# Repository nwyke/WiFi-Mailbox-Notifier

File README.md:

# WiFi Mailbox Notifier

This board notifies you when you get mail. JST-PH connector for 3.7V lithium ion battery (min 500mA), USB connector for power and battery charging, auto-reset for ESP-module, battery voltage measurement. 

Inspired by [hal9k "postkasse overvaagning"](https://hal9k.dk/postkasse-overvaagning/). Boards can be found on [OSHPark](https://oshpark.com/shared_projects/7UJ1nXM0) (not tested yet!).

Please support us and open-source hardware by purchasing products from
[MiniElektro.dk](http://minielektro.dk)/[MiniElektro.se](http://minielektro.se).

Content
-------------------
* **/Hardware**
  * All Eagle design files (.brd, .sch)
  * PDF schematic
  * BOM

License
-------------------
The hardware is released under [Creative Commons ShareAlike 4.0 International](https://creativecommons.org/licenses/by-sa/4.0/).

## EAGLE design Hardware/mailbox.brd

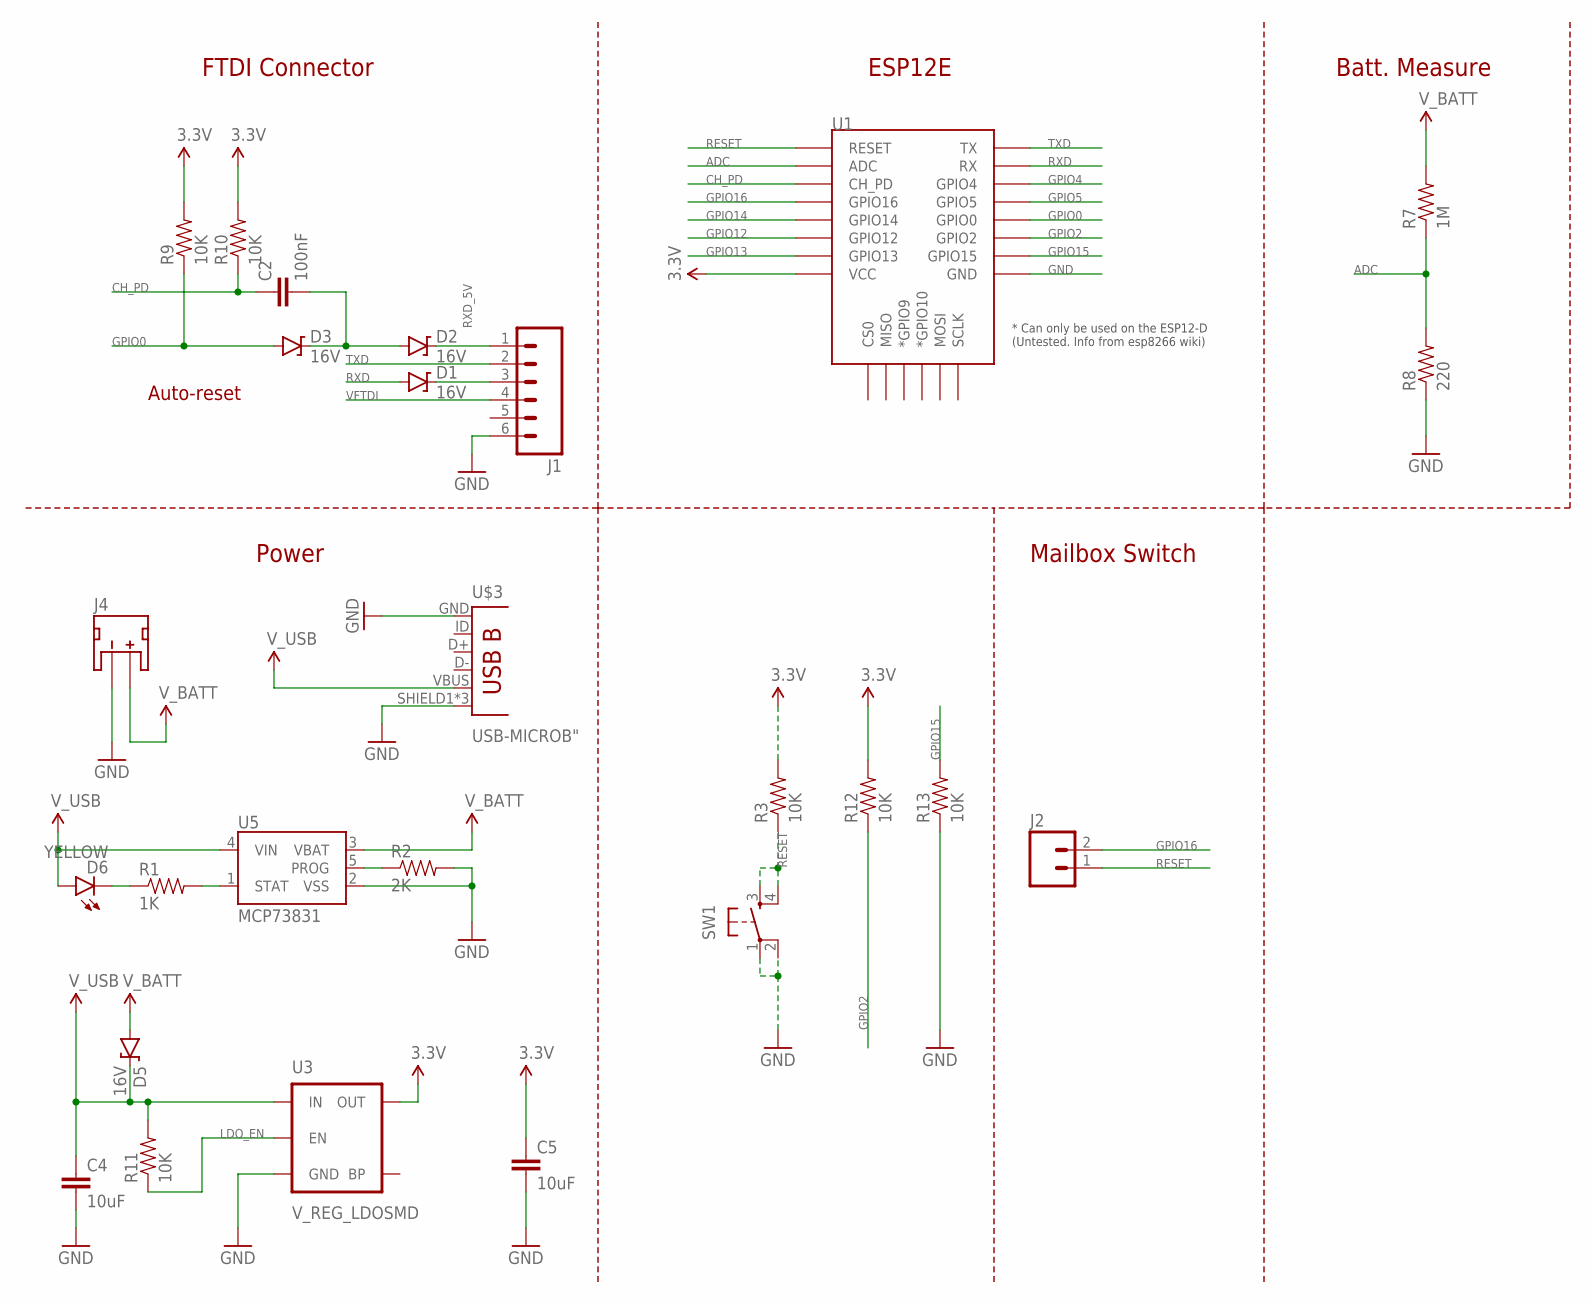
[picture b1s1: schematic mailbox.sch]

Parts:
C2: 100nF; 1206
C4, C5: 10uF; 1206
D1, D2, D3, D5: 16V; SOD-123
D6: YELLOW; LED-1206
J1: M06SILK_FEMALE_PTH; 1X06
J2: M02LOCK; 1X02_LOCK
J4: JST_2MM_MALE; JST-2-SMD
R1: 1K; 1206
R2: 2K; 1206
R3, R9, R10, R11, R12, R13: 10K; 1206
R7: 1M; 1206
R8: 220; 1206
SW1: SWITCH_SPST_4_PINRECT; TACTILE_SWITCH_SMD_4.6X2.8MM
U1: ESP12ESMD; ESP12E-SMD
U3: V_REG_LDOSMD; SOT23-5
U5: MCP73831; SOT23-5
U$3: USB-MICROB"; USB-B-MICRO-SMD_V03

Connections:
3.3V: C5.1, R3.2, R9.2, R10.2, R12.2, U1.VCC, U3.5 (OUT)
ADC: R7.1, R8.2, U1.ADC
CH_PD: C2.1, R10.1, U1.CH_PD
GND: C4.2, C5.2, J1.6, J4.1 (-), R2.2, R8.1, R13.1, SW1.1, SW1.2, U1.GND, U3.2 (GND), U5.2 (VSS), U$3.GND, U$3.SHIELD1 (SHIELD), U$3.SHIELD2 (SHIELD), U$3.SHIELD3 (SHIELD)
GPIO0: D3.A, R9.1, U1.GPIO0
GPIO2: R12.1, U1.GPIO2
GPIO4: U1.GPIO4
GPIO5: U1.GPIO5
GPIO12: U1.GPIO12
GPIO13: U1.GPIO13
GPIO14: U1.GPIO14
GPIO15: R13.2, U1.GPIO15
GPIO16: J2.2, U1.GPIO16
LDO_EN: R11.1, U3.3 (EN)
unnamed: D6.C, R1.1
unnamed: D2.C, J1.1
unnamed: C2.2, D2.A, D3.C
unnamed: R1.2, U5.1 (STAT)
unnamed: R2.1, U5.5 (PROG)
RESET: J2.1, R3.1, SW1.3, SW1.4, U1.RESET
RXD: D1.A, U1.RXD0 (RX)
RXD_5V: D1.C, J1.3
TXD: J1.2, U1.TXD0 (TX)
VFTDI: J1.4
V_BATT: D5.A, J4.2 (+), R7.2, U5.3 (VBAT)
V_USB: C4.1, D5.C, D6.A, R11.2, U3.1 (IN), U5.4 (VIN), U$3.VBUS

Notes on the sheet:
FTDI Connector
Auto-reset
ESP12E
Power
Mailbox Switch
Batt. Measure

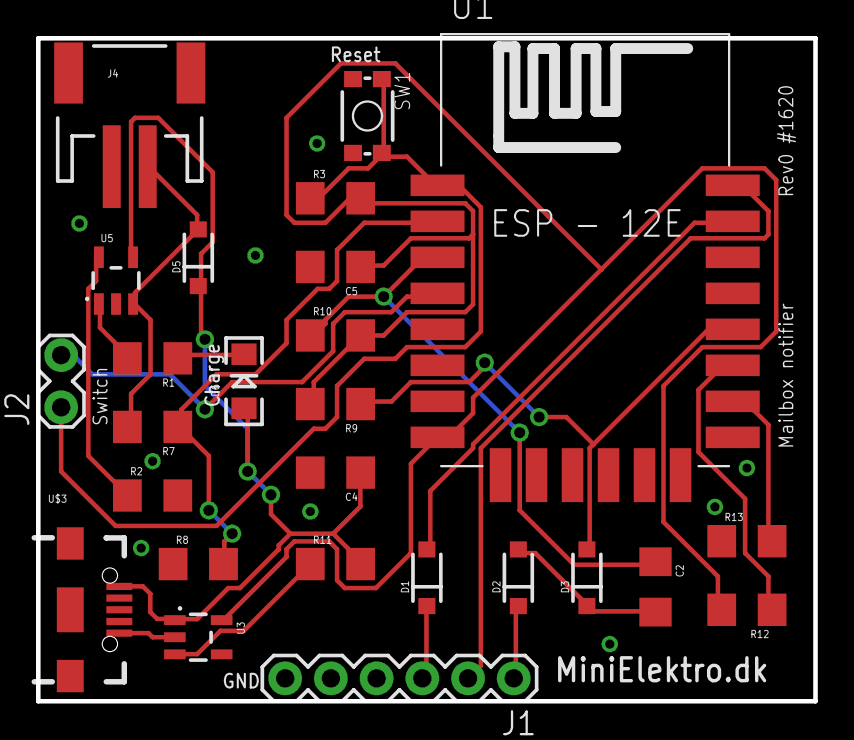
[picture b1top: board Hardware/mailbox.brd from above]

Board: 2 copper layers, 43.2 x 36.8 mm, 26 parts (0 on the bottom side), 20 nets.

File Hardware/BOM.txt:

Part Value        Device                Package                      Description          BTM_NEG BTM_POS PROD_ID    TOP_NEG TOP_POS VALUE 
C2   100nF        CAP1206               1206                         Capacitor                                                             
C4   10uF         CAP1206               1206                         Capacitor                                                             
C5   10uF         CAP1206               1206                         Capacitor                                                             
D1   16V          DIODE-ZENER16V        SOD-123                      Zener Diode                          DIO-12440                  16V   
D2   16V          DIODE-ZENER16V        SOD-123                      Zener Diode                          DIO-12440                  16V   
D3   16V          DIODE-ZENER16V        SOD-123                      Zener Diode                          DIO-12440                  16V   
D5   16V          DIODE-ZENER16V        SOD-123                      Zener Diode                          DIO-12440                  16V   
D6   YELLOW       LED-YELLOW1206        LED-1206                     Yellow SMD LEDs                      DIO-00820                  YELLOW
J1                M06SILK_FEMALE_PTH    1X06                         Header 6                             CONN-08437                       
J2                M02LOCK               1X02_LOCK                    Standard 2-pin 0.1"                                                   
J4                JST_2MM_MALE          JST-2-SMD                    Mates to single-cell -       +       CONN-11443 -       +             
R1   1K           RESISTOR1206          1206                         Resistor                                                              
R2   2K           RESISTOR1206          1206                         Resistor                                                              
R3   10K          RESISTOR1206          1206                         Resistor                                                              
R7   1M           RESISTOR1206          1206                         Resistor                                                              
R8   220          RESISTOR1206          1206                         Resistor                                                              
R9   10K          RESISTOR1206          1206                         Resistor                                                              
R10  10K          RESISTOR1206          1206                         Resistor                                                              
R11  10K          RESISTOR1206          1206                         Resistor                                                              
R12  10K          RESISTOR1206          1206                         Resistor                                                              
R13  10K          RESISTOR1206          1206                         Resistor                                                              
SW1               SWITCH_SPST_4_PINRECT TACTILE_SWITCH_SMD_4.6X2.8MM                                      SWCH-13065                       
U$3  USB-MICROB"  USB-MICROB"           USB-B-MICRO-SMD_V03                                               CONN-11752                       
U1                ESP12ESMD             ESP12E-SMD                   ESP12E Module                                                         
U3   V_REG_LDOSMD V_REG_LDOSMD          SOT23-5                      Voltage Regulator LD                                                  
U5   MCP73831     MCP73831              SOT23-5

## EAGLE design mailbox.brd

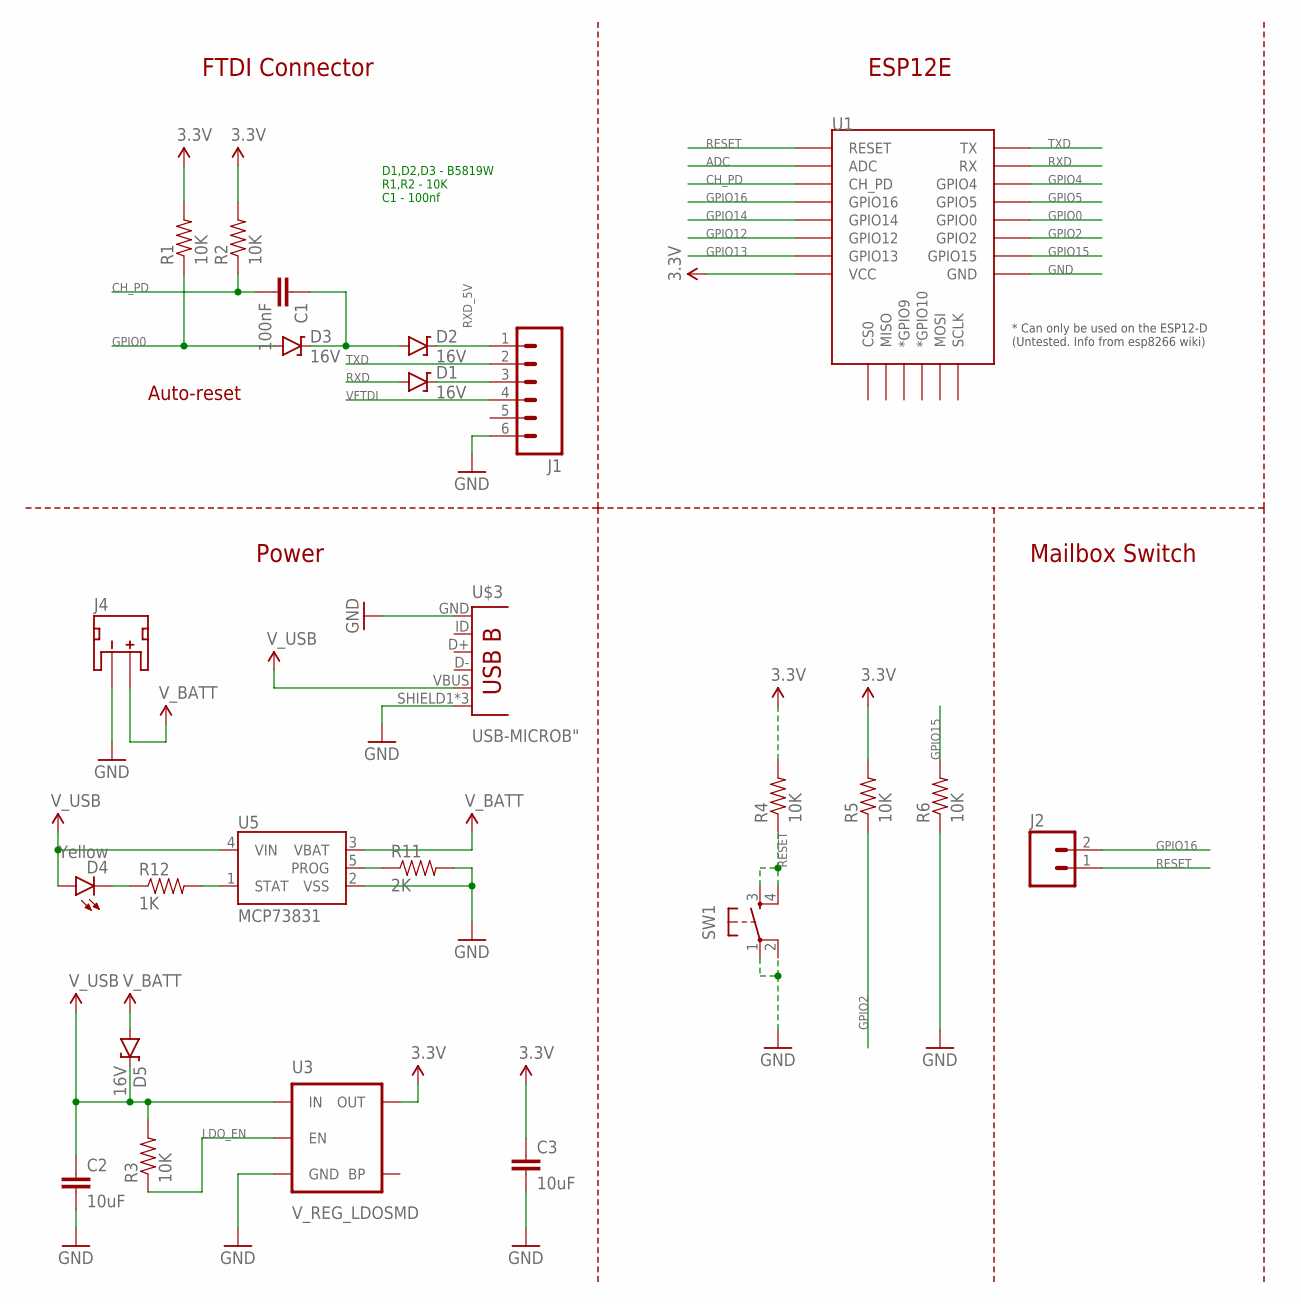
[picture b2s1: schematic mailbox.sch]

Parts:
C1: 100nF; 0402-CAP
C2, C3: 10uF; 0402-CAP
D1, D2, D3, D5: 16V; SOD-123
D4: Yellow; LED-0603
J1: M06SILK_FEMALE_PTH; 1X06
J2: M02LOCK; 1X02_LOCK
J4: JST_2MM_MALE; JST-2-SMD
R1, R2, R3, R4, R5, R6: 10K; 0402-RES
R11: 2K; 0603-RES
R12: 1K; 0603-RES
SW1: SWITCH_SPST_4_PINRECT; TACTILE_SWITCH_SMD_4.6X2.8MM
U1: ESP12ESMD; ESP12E-SMD
U3: V_REG_LDOSMD; SOT23-5
U5: MCP73831; SOT23-5
U$3: USB-MICROB"; USB-B-MICRO-SMD_V03

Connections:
3.3V: C3.1, R1.2, R2.2, R4.2, R5.2, U1.VCC, U3.5 (OUT)
ADC: U1.ADC
CH_PD: C1.2, R2.1, U1.CH_PD
GND: C2.2, C3.2, J1.6, J4.1 (-), R6.1, R11.2, SW1.1, SW1.2, U1.GND, U3.2 (GND), U5.2 (VSS), U$3.GND, U$3.SHIELD1 (SHIELD), U$3.SHIELD2 (SHIELD), U$3.SHIELD3 (SHIELD)
GPIO0: D3.A, R1.1, U1.GPIO0
GPIO2: R5.1, U1.GPIO2
GPIO4: U1.GPIO4
GPIO5: U1.GPIO5
GPIO12: U1.GPIO12
GPIO13: U1.GPIO13
GPIO14: U1.GPIO14
GPIO15: R6.2, U1.GPIO15
GPIO16: J2.2, U1.GPIO16
LDO_EN: R3.1, U3.3 (EN)
unnamed: D4.C, R12.1
unnamed: D2.C, J1.1
unnamed: C1.1, D2.A, D3.C
unnamed: R12.2, U5.1 (STAT)
unnamed: R11.1, U5.5 (PROG)
RESET: J2.1, R4.1, SW1.3, SW1.4, U1.RESET
RXD: D1.A, U1.RXD0 (RX)
RXD_5V: D1.C, J1.3
TXD: J1.2, U1.TXD0 (TX)
VFTDI: J1.4
V_BATT: D5.A, J4.2 (+), U5.3 (VBAT)
V_USB: C2.1, D4.A, D5.C, R3.2, U3.1 (IN), U5.4 (VIN), U$3.VBUS

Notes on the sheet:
D1,D2,D3 - B5819W R1,R2 - 10K C1 - 100nf
FTDI Connector
Auto-reset
ESP12E
Power
Mailbox Switch

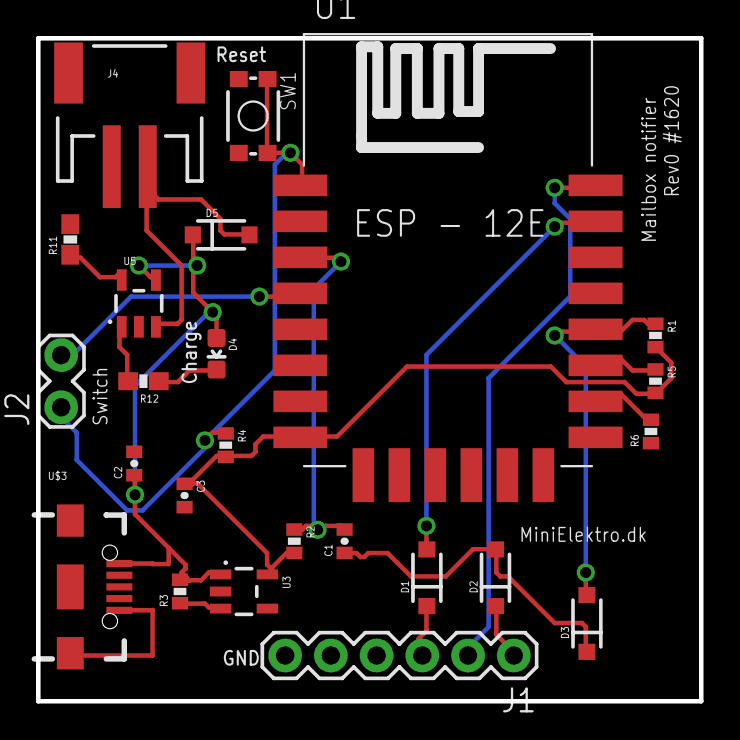
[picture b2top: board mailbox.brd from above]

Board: 2 copper layers, 36.8 x 36.8 mm, 24 parts (0 on the bottom side), 19 nets.

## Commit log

2016-05-16 Initial
2016-05-17 Added battery measure + PDF schematic
2016-05-17 Added OSHPark link
2016-05-17 Create BOM
2016-05-20 Update license

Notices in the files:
parts and their libraries:
SparkFun-Passives: Licensing: Creative Commons ShareAlike 4.0 International - https://creativecommons.org/licenses/by-sa/4.0
